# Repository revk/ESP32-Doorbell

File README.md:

## Trademark

This is an open source project, but bear in mind you cannot sell boards bearing the Andrews & Arnold Ltd name, the A&A logo, the registered trademark AJK logo, or the GS1 allocated EANs assigned to Andrews & Arnold Ltd.

# ESP32-Doorbell

This project is designed to provide an interactive doorbell sign. It can connect to a bell push directly.

The concept is simple, the sign shows a suitable idle message (e.g. house number) but on bell push changes to a different message. The system has automatic seasonal variations on the idle message.

The simple case is a "please wait, we are on the way" messaged to acknowledge the bell push, but it can be customised via web hooks or MQTT or tracking the state of tasmota switches. This means a message could be different when "out" (e.g. leave behind gates, or in secure bin, etc), but without that message on the door all the time.

The bell push itself typically works a bell via MQTT, such as a tasmota switch.

The code runs on an ESP32-S3 and uses the PCB designs from [ESP32-GFX EPD75](https://github.com/revk/ESP32-GFX/tree/main/PCB/EPD75). This includes an LED in each corner and fits the Waveshare 7.5" e-paper. The Waveshare is available with laminated glass front as per this image, and the PCB needs a waterproof coating. Be wary of encasing in resin as the FPC connector can stop working.

[Manual](Manual/Manual.md)

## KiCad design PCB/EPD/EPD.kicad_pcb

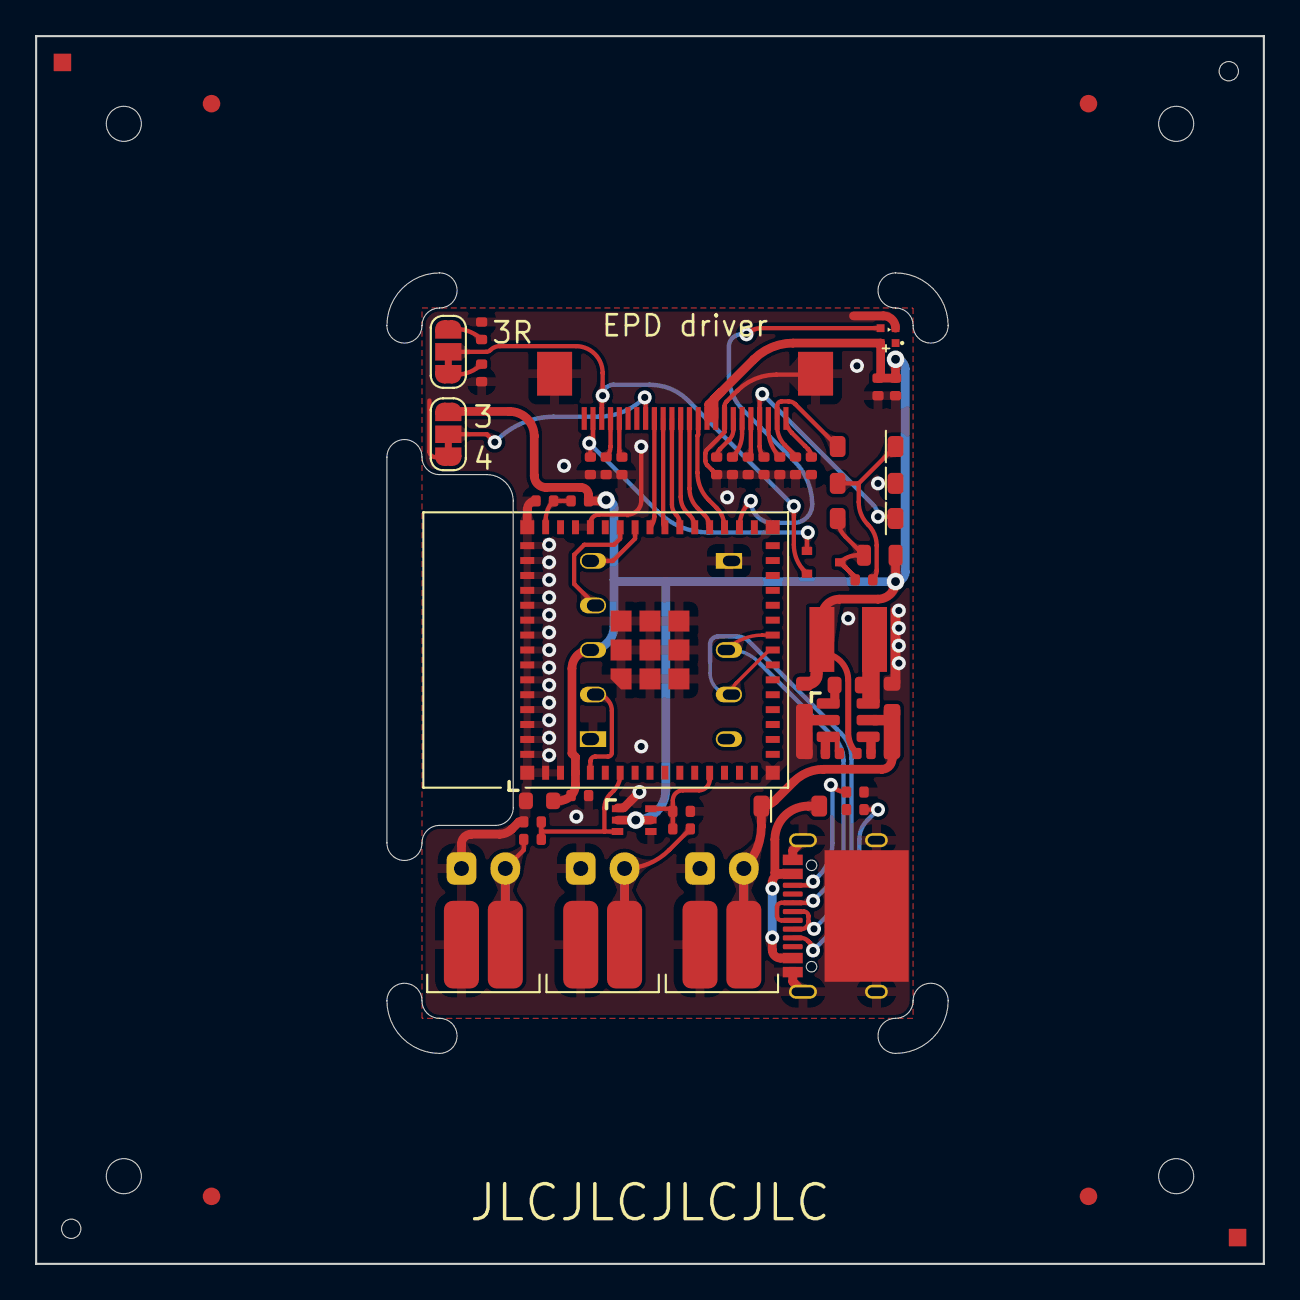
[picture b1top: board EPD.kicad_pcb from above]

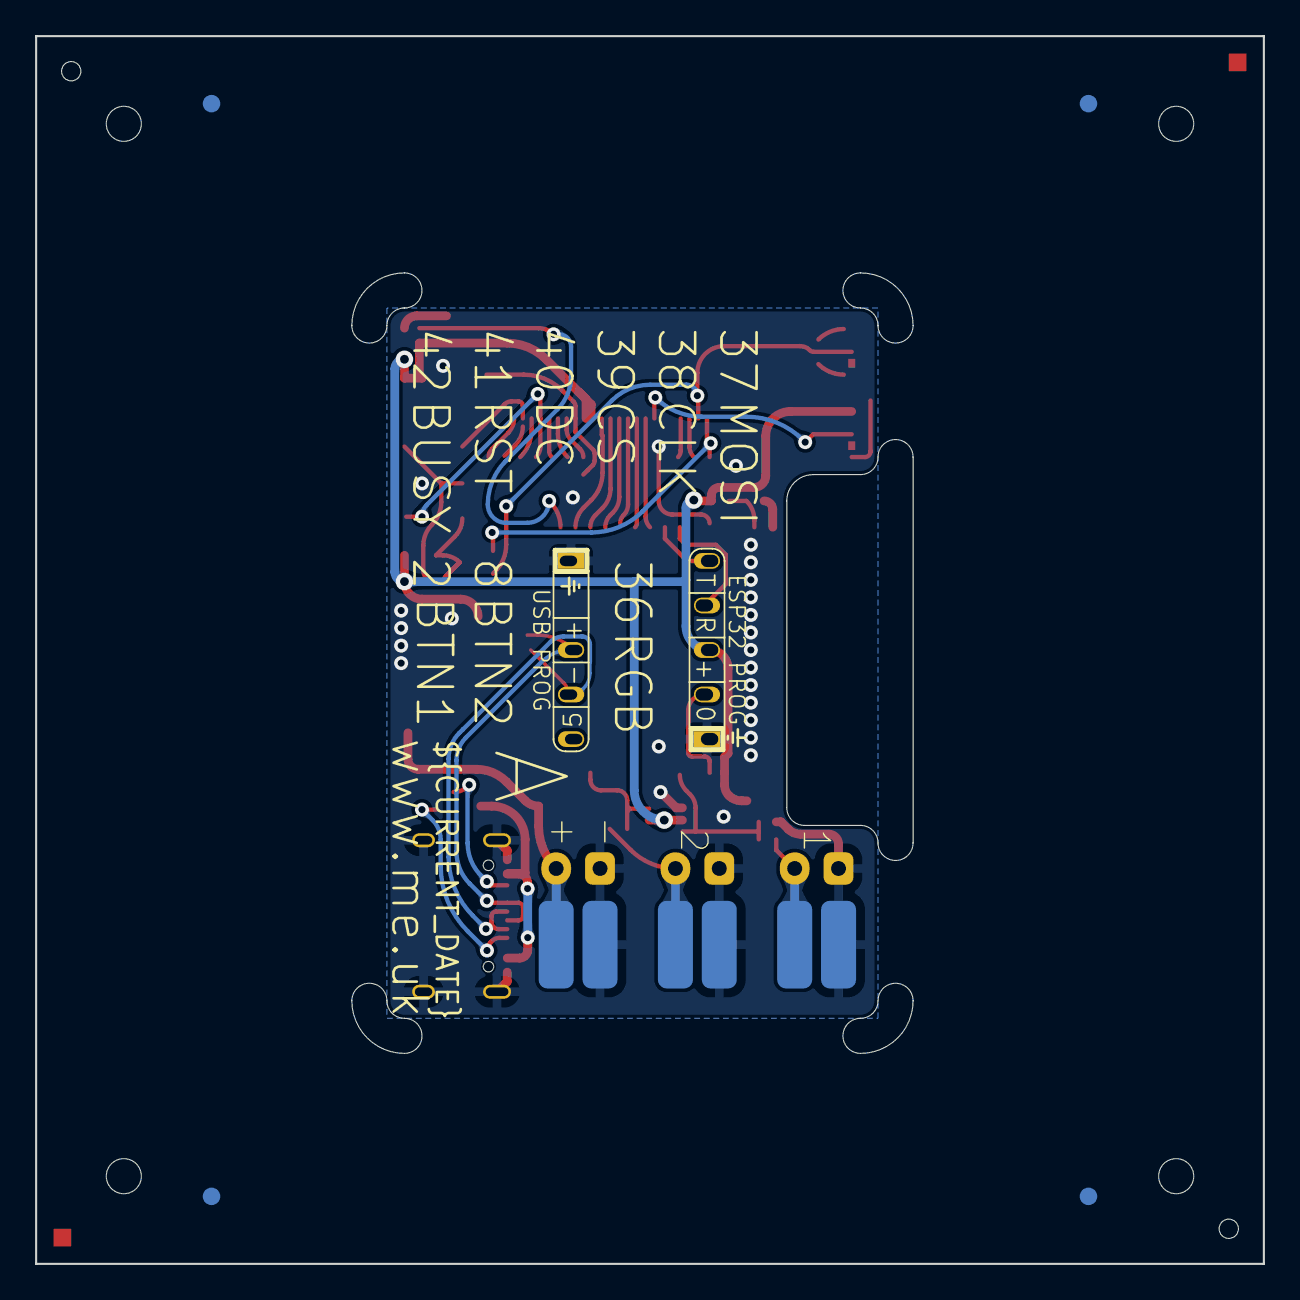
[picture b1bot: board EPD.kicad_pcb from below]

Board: 2 copper layers, 70.0 x 70.0 mm, 68 parts (10 on the bottom side), 39 nets.

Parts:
C1, C3, C4, C7, C11, C12, C13, C15, C16: 1uF 50V; C_0402
C2: 100nF; C_0402
C5: 22uF; C_0603
C6: 1uF; C_0402
C8: 10uF 50V; C_0603_
C9: 10uF 6.3V; C_0603_
C10: 100nF; C_0603_
C14: 100nF 50V; C_0402
C17: 4.7uF; C_0402
C18: 10uF; C_0402
C21, C22: 33pF; C_0402
D1, D2, D3: 1N5819W; D_SOD-123
D4: XL-1010RGBC-WS2812B; SMD1010
D6: D; D_SOD-123
D7: BAV99S; SOT-363_SC-70-6
J1: Conn_01x26; XUNPU-FPC-05FB-24PH20
J2: Shelly
J3: USB-PROG
J4: BTN1; PTSM-HH-2-RA
J6: BTN2; PTSM-HH-2-RA
J7: USB-C-Socket-V; USB-C-Socket-H
J8: PWR; PTSM-HH-2-RA
JP1, JP2: SolderJumper_3_Bridged12; SolderJumper3
L1: 68uH; L_0805
L2: 10uH; L_4x4_
P1, P7: +; SolderPadSmall
P2, P8: -; SolderPadSmall
P3, P4, P9, P10: 2; SolderPadSmall
P5, P6, P11, P12: 1; SolderPadSmall
PCB1: 70x70; PCB7070
Q1: DMG1012T; SOT-323_SC-70-3
R1: 0.47R; R_0402
R2, R3: 10K; R_0402
R4, R5: 5k1; R_0402
R6, R7: 100R; R_0402
R8: 3R; R_0402
R9: 124k; R_0402_
R10: 39k2; R_0402_
R11: 1M; R_0402_
U3: MD8942; SOT-23-6-MD8942
U4: ESP32-S3-MINI-1
V1, V3, V4, V6: VCUT70N

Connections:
+3.3V: C2.1, C5.1, C14.1, C18.2, D4.2 (+), D7.2 (K2), D7.5 (K4), J1.15, J1.16, J2.3 (3V3), JP1.3 (B), L1.2, R3.1, U3.8 (VOUT), U4.3 (3V3)
BTN1: C22.1, D7.3 (K1A2), R7.2, U4.6 (GPIO2)
BTN2: C21.1, D7.6 (K3A4), R6.2, U4.12 (GPIO8)
BUSY: J1.9, U4.38 (GPIO42)
CLK: J1.13, U4.34 (GPIO38)
CS: J1.12, U4.35 (GPIO39)
D+: J3.3 (D+), J7.A6 (D+), J7.B6 (D+), U4.24 (GPIO20)
D-: J3.2 (D-), J7.A7 (D-), J7.B7 (D-), U4.23 (GPIO19)
DC: J1.11, U4.36 (GPIO40)
GND: C1.2, C2.2, C3.2, C4.2, C5.2, C6.2, C7.2, C11.2, C12.2, C13.2, C14.2, C15.2, C16.2, C18.1, C21.2, C22.2, D3.1 (K), D4.3 (-), D7.1 (A1), D7.4 (A3), J1.17, J1.25, J1.26, J2.1 (GND), J3.4 (GND), J4.1, J6.1, J7.A1 (GND), J7.A12 (GND), J7.B1 (GND), J7.B12 (GND), J7.S1 (SHIELD), J8.1, JP1.1 (A), P2.1, P4.1, P6.1, P8.1, P10.1, P12.1, R1.2, R2.1, R4.2, R5.2, R8.1, U3.2 (GND), U3.7 (GND), U4.1 (GND), U4.2 (GND), U4.42 (GND), U4.43 (GND), U4.46 (GND), U4.47 (GND), U4.48 (GND), U4.49 (GND), U4.50 (GND), U4.51 (GND), U4.52 (GND), U4.53 (GND), U4.54 (GND), U4.55 (GND), U4.56 (GND), U4.57 (GND), U4.58 (GND), U4.59 (GND), U4.60 (GND), U4.61 (GND), U4.62 (GND), U4.63 (GND), U4.64 (GND), U4.65 (GND)
MOSI: J1.14, U4.33 (GPIO37)
unnamed: C3.1, D1.2 (A), J1.23
unnamed: C17.2, D1.1 (K), D3.2 (A)
unnamed: C17.1, D2.2 (A), L1.1, Q1.3 (D)
unnamed: C7.1, D2.1 (K), J1.21
unnamed: D6.2 (A), J7.A4 (VBUS), J7.A9 (VBUS), J7.B4 (VBUS), J7.B9 (VBUS)
unnamed: J1.2, Q1.1 (G), R2.2
unnamed: J1.3, JP2.2 (C), Q1.2 (S)
unnamed: C16.1, J1.4
unnamed: C15.1, J1.5
unnamed: J1.8, JP1.2 (C)
unnamed: C13.1, J1.18
unnamed: C12.1, J1.19
unnamed: C11.1, J1.20
unnamed: C4.1, J1.22
unnamed: C1.1, J1.24
unnamed: J2.2 (0), U4.4 (GPIO0)
unnamed: J2.4 (Rx), U4.40 (GPIO44)
unnamed: J2.5 (Tx), U4.39 (GPIO43)
unnamed: J4.2, P5.1, P11.1, R7.1
unnamed: J6.2, P3.1, P9.1, R6.1
unnamed: J7.A5 (CC1), R4.1
unnamed: J7.B5 (CC2), R5.1
unnamed: JP2.1 (A), R1.1
unnamed: JP2.3 (B), R8.2
unnamed: C6.1, R3.2, U4.45 (EN)
PWR: D6.1 (K), J8.2, P1.1, P7.1, U3.5 (VIN)
RGB: D4.4 (I), U4.32 (GPIO36)
RST: J1.10, U4.37 (GPIO41)

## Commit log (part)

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2023-12-11 Library update
2023-12-15 relay
2023-12-15 checkpoint
2023-12-22 Startup screen
2023-12-22 Idle white range
2023-12-23 Tidy
2023-12-23 EPD75R
2023-12-27 More info
2023-12-29 Use library
2024-01-08 Cache images
2024-01-11 mutex... But still no clue why crashed
2024-01-12 More stack
2024-01-12 Stack
2024-01-13 Even more stack?!
2024-01-13 more logging
2024-01-13 Reinforce image
2024-01-13 Logging
2024-01-29 New settings
2024-02-02 beta
2024-02-06 release
2024-02-09 Silly
2024-02-27 SD card
2024-03-11 link down check
2024-04-16 Test
2024-11-12 Library
2024-12-18 MMC mode
2024-12-19 NFC LED state tracking
2024-12-19 Blink/solid logic
2024-12-19 more blink
2024-12-20 NFC monitoring and LED logic
2025-02-11 Settings
2025-02-11 Rework release and settings
2025-02-11 defaults
2025-02-18 gfxnight
2025-03-02 Change to PNG based
2025-03-02 No reinforce, done by gfx now
2025-03-03 New call
2025-03-03 New calls
2025-03-06 Default
2025-03-06 Typo
2025-03-06 Start on frame logic
2025-03-06 Show current frame buffer
2025-03-06 Colour coding
2025-03-06 Frame view
2025-03-12 Tidy IPv6
2025-03-12 IP tidy
2025-03-22 tarted tidy of season logic
2025-03-22 Reworked a lot
2025-03-22 More overlay logic
2025-03-22 Date
2025-03-22 Cleaner startup
2025-03-22 Slow update, gets attention though
2025-03-26 Allow EPD tweaks
2025-04-16 Update library
2025-04-16 Debounce
2025-11-15 app update
2026-02-15 Codeberg
